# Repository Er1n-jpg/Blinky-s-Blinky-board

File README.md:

# Blinky Board
I was today years old when I found out the red ghost in pac-man was named blinky, so this is why I made a blinky board THAT LOOKS LIKE BLINKY!! Blinky has 10 LEDs on him, 2 for his eyes and the other 8 for his mouth (im not really sure that the ghosts actually have mouths in pacman but lets pretend lol)

# Why did I make this?
Realistically this project doesn't have some meaningful earth shattering purpose, I just started it because I wanted a project to finish the very minimal amount of fallout debt I had left, all while giving me some review of how a 555 timer works (I did not understand that unit from my computer engineering class).
Usually a blinky is someone's first hardware project but it's actually my third. But hey its never too late to make one yk?

# How to assemble a blinky!
Step 1: Gather all of your pcb parts along with your pcb and sort out what goes where according to the 3d view and schematics provided in the production folder

Step 2: Grab a soldering iron and some flux and start soldering!

Step 3: Plug into a power source and watch your blinky go!

# Proccess

The initial schematic^^

Blinky with all it's traces^^

3D view of the PCB^^

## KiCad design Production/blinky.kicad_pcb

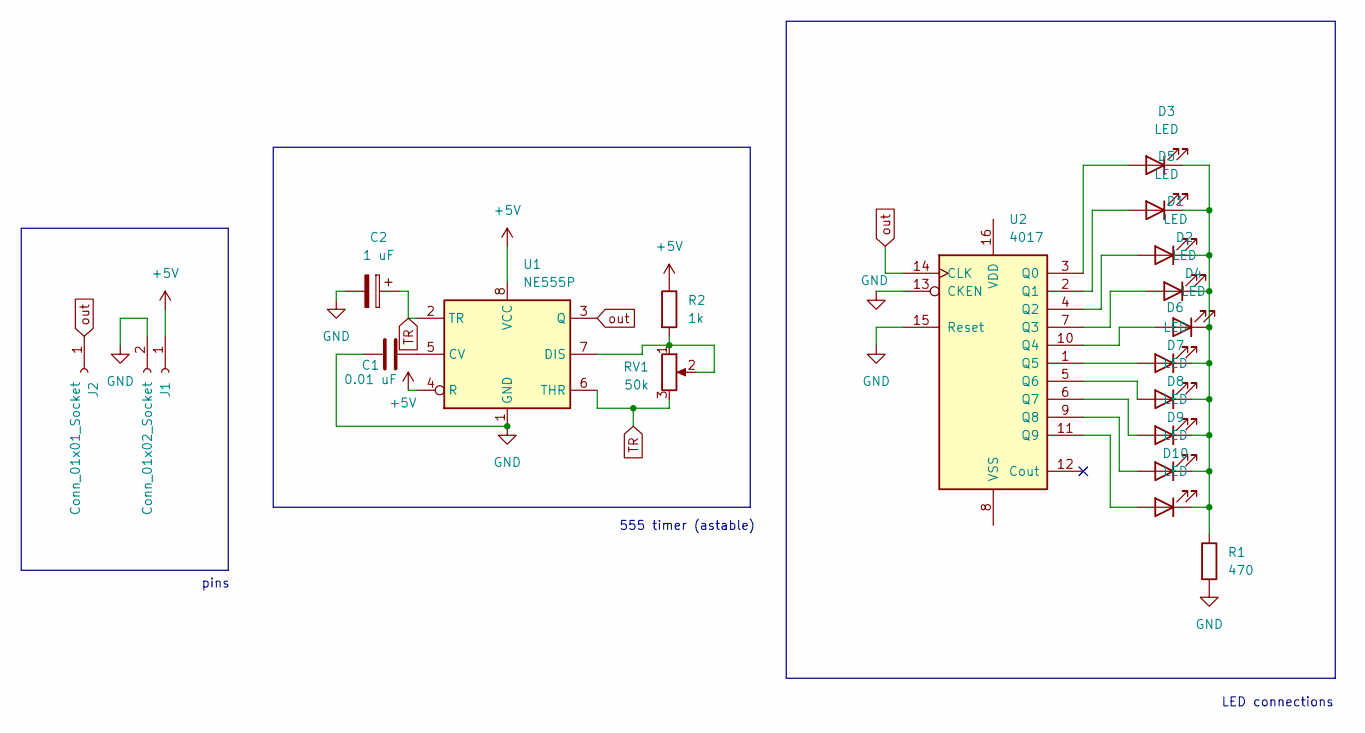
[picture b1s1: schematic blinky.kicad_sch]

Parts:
C1: 0.01 uF; CP_Radial_D5.0mm_P2.00mm
C2: 1 uF; C_Disc_D7.5mm_W2.5mm_P5.00mm
D1, D2, D3, D4, D5, D6, D7, D8, D9, D10: LED; LED_D3.0mm
J1: Conn_01x02_Socket; PinHeader_1x02_P2.54mm_Vertical
J2: Conn_01x01_Socket; PinHeader_1x01_P2.54mm_Vertical
R1: 470; R_Axial_DIN0207_L6.3mm_D2.5mm_P7.62mm_Horizontal
R2: 1k; R_Axial_DIN0207_L6.3mm_D2.5mm_P10.16mm_Horizontal
RV1: 50k; Potentiometer_Vishay_T93YA_Vertical
U1: NE555P; DIP-8_W7.62mm
U2: 4017; N16

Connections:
+5V: J1.1, R2.1, U1.4 (R), U1.8 (VCC)
GND: C1.1, C2.2, J1.2, R1.2, U1.1 (GND), U2.13 (CKEN), U2.15 (Reset)
unnamed: D1.2 (A), U2.4 (Q2)
unnamed: D1.1 (K), D2.1 (K), D3.1 (K), D4.1 (K), D5.1 (K), D6.1 (K), D7.1 (K), D8.1 (K), D9.1 (K), D10.1 (K), R1.1
unnamed: D2.2 (A), U2.7 (Q3)
unnamed: D3.2 (A), U2.3 (Q0)
unnamed: D4.2 (A), U2.10 (Q4)
unnamed: D5.2 (A), U2.2 (Q1)
unnamed: D6.2 (A), U2.1 (Q5)
unnamed: D7.2 (A), U2.5 (Q6)
unnamed: D8.2 (A), U2.6 (Q7)
unnamed: D9.2 (A), U2.9 (Q8)
unnamed: D10.2 (A), U2.11 (Q9)
unnamed: C1.2, U1.5 (CV)
unnamed: R2.2, RV1.1, RV1.2, U1.7 (DIS)
TR: C2.1, RV1.3, U1.2 (TR), U1.6 (THR)
out: J2.1, U1.3 (Q), U2.14 (CLK)

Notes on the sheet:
LED connections
555 timer (astable)
pins

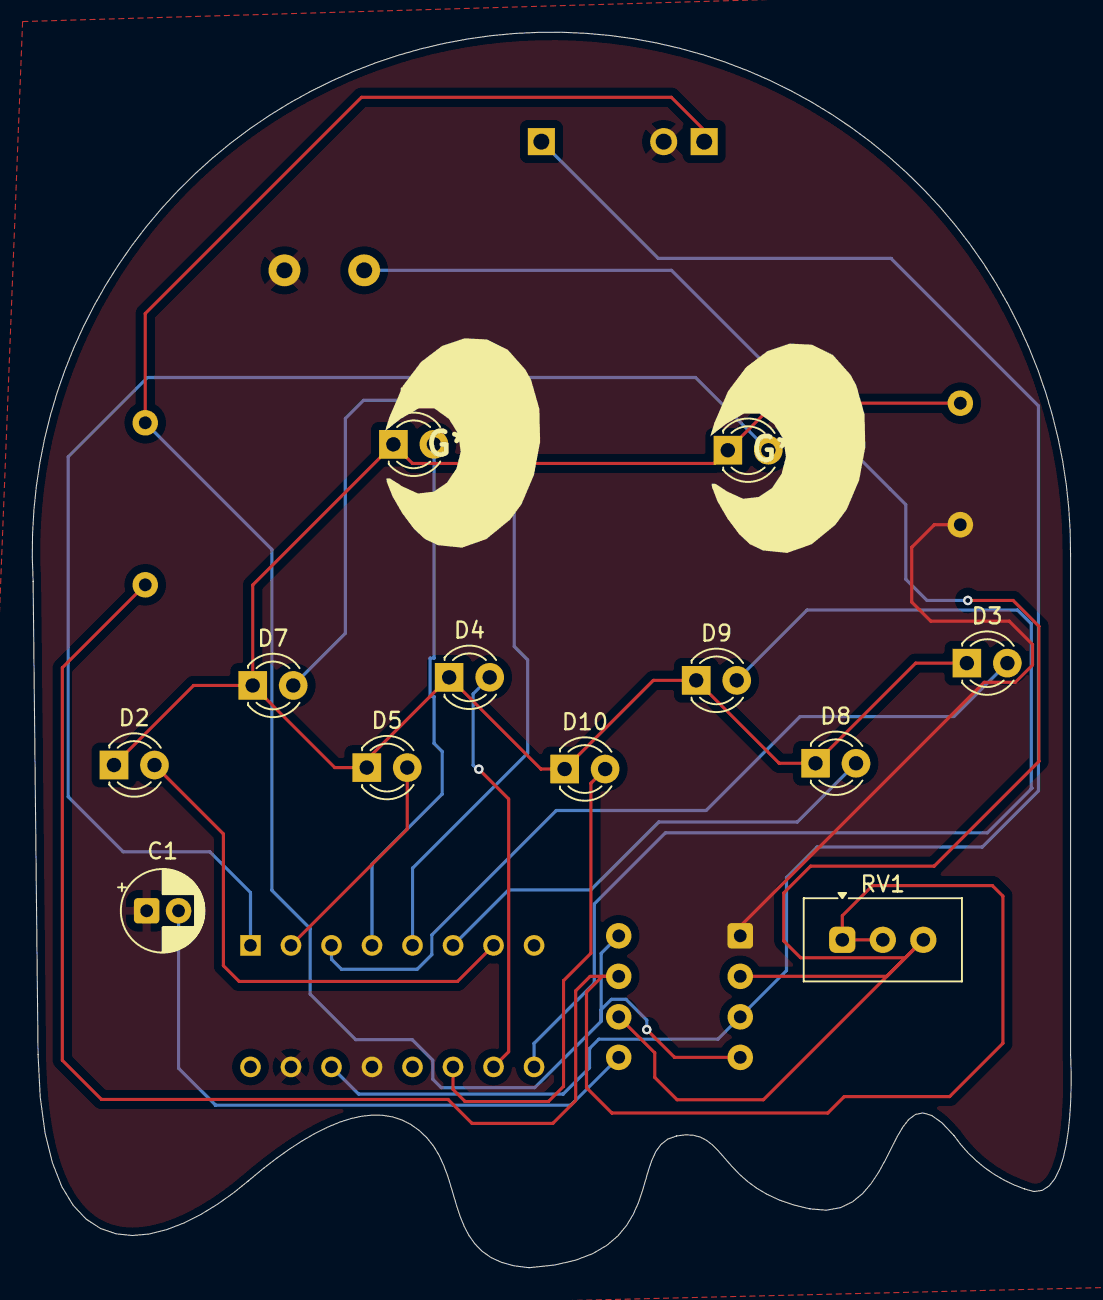
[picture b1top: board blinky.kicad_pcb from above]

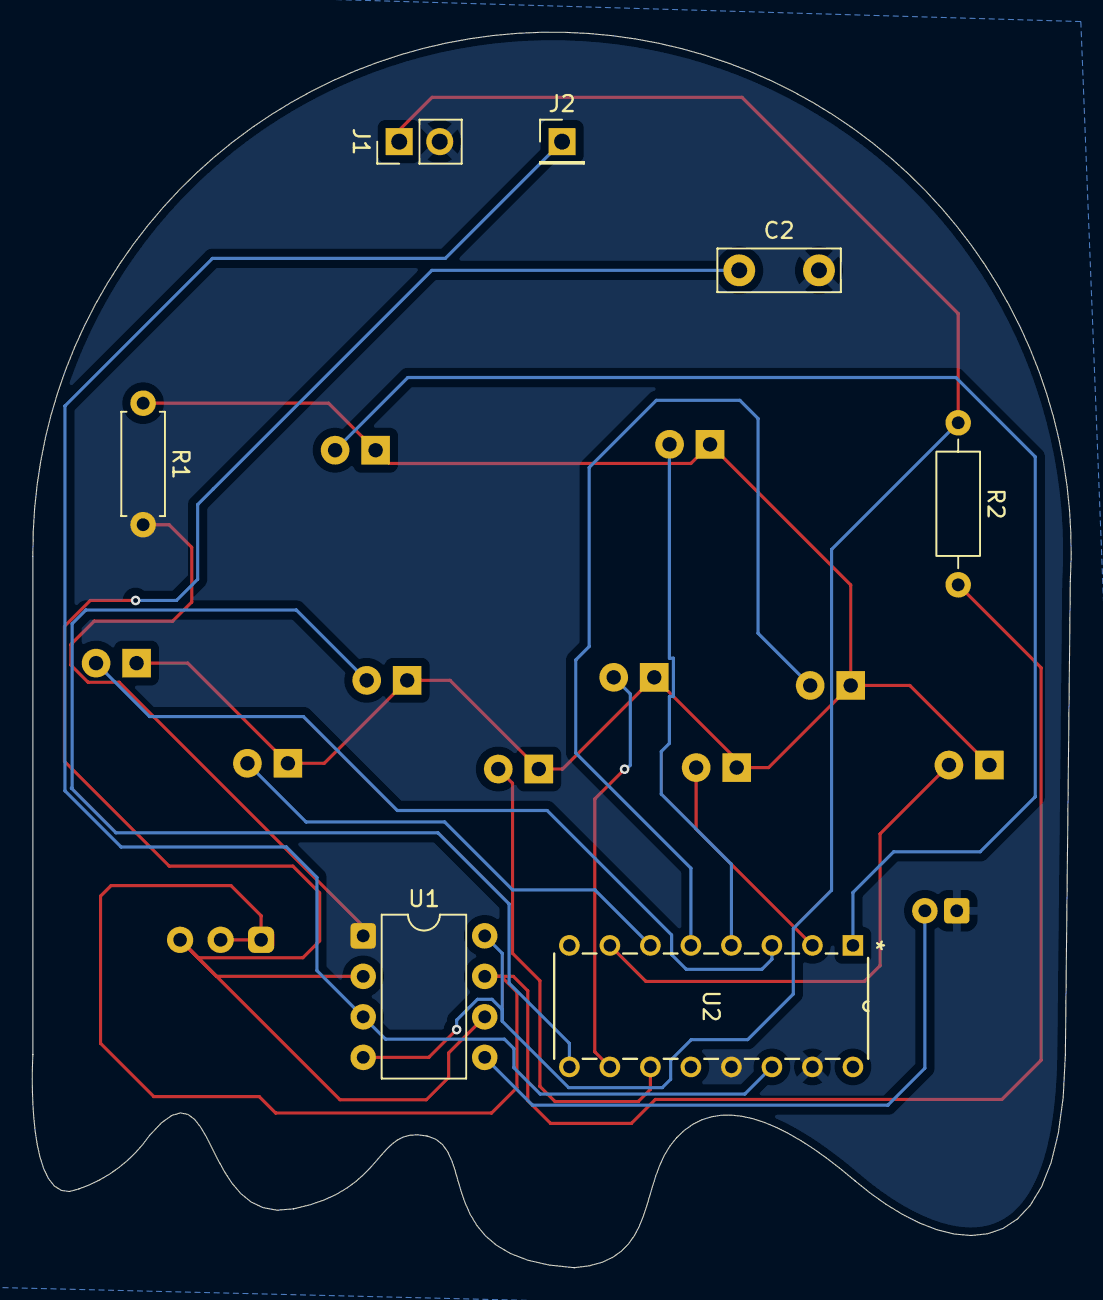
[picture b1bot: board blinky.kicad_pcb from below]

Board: 2 copper layers, 65.1 x 77.5 mm, 19 parts (7 on the bottom side), 17 nets.
